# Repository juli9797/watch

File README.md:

# WATCH   

This is a simple LED-wristwatch with 16 LEDs and one push button.
Everything is controlled by a STM32F103 and its realtime clock.
Time is visualized using 12 LEDs for the hours and 5 minute steps and 4 additional LEDs to indicate minute%5 .
The current hour LED will light up steady while the minute LEDs flash slowly.

## Specs:   
* handles 1S LIPO
* 38mm diameter
* 4 Layer PCB
* exposed I2C and UART interface for future extensions

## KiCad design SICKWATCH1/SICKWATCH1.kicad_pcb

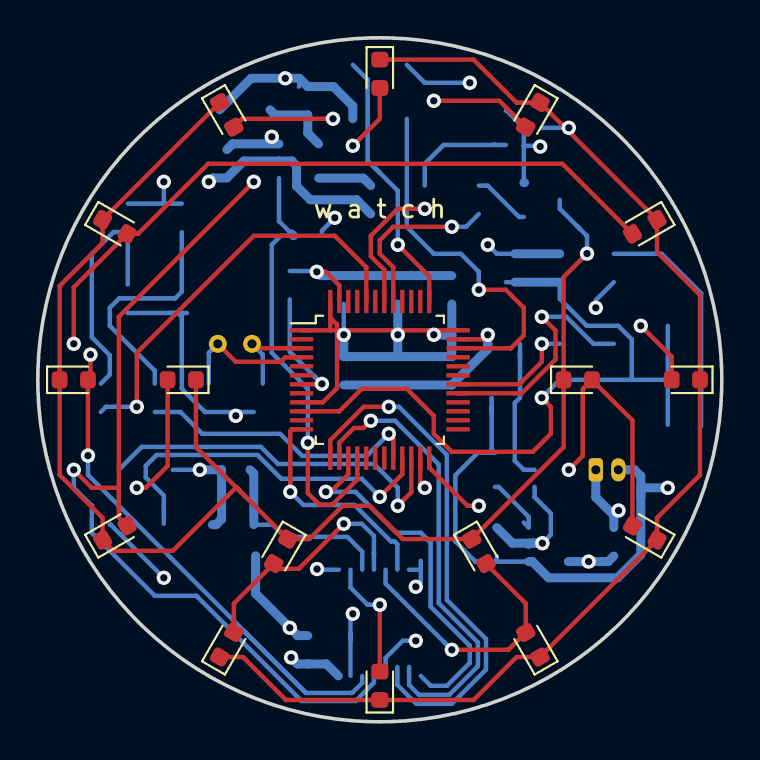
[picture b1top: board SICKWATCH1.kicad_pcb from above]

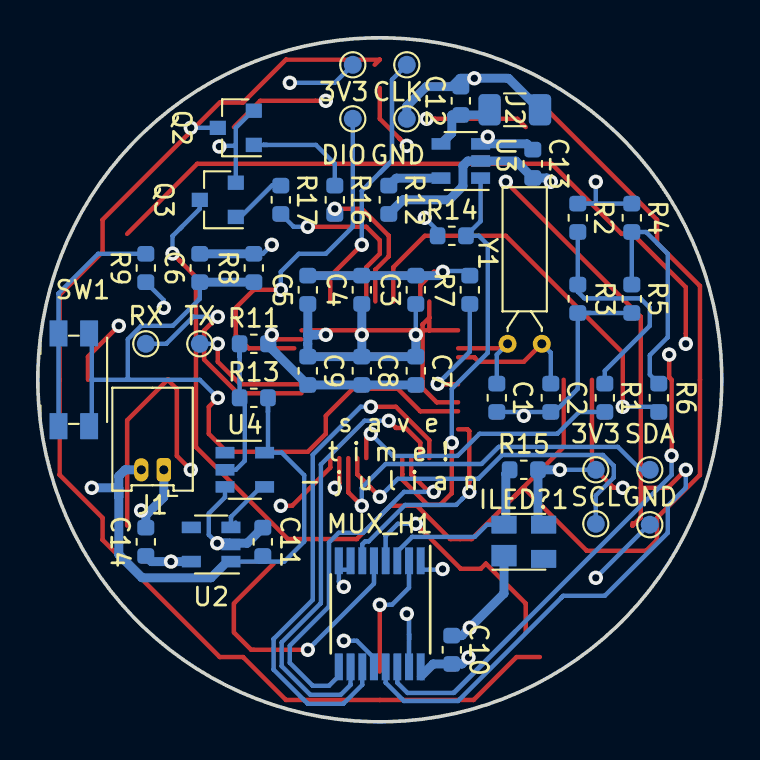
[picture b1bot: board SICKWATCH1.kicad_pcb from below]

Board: 4 copper layers, 38.0 x 38.0 mm, 68 parts (51 on the bottom side), 42 nets.

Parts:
C1, C2, C6, C10: C; C_0603_1608Metric
C3, C13: 4u7; C_0603_1608Metric
C4, C5, C7, C8, C9, C11, C14: 100n; C_0603_1608Metric
C12: 100nF; C_0603_1608Metric
D1, D2, D3, D4, D5, D6, D7, D8, D9, D10, D11, D12, D13, D14, D15, D16: LED; LED_0603_1608Metric
ILED?1: BCR401; SOT-143R_Reverse
J1: Conn_01x02_Female; Molex_PicoBlade_53048-0210_1x02_P1.25mm_Horizontal
J2: Conn_01x02_Female; R_1206_3216Metric
MUX_H1: SN74LV4051A; TSSOP-16_4.4x5mm_P0.65mm
Q2, Q3: BSS138; SOT-23
R1, R6: 100k; R_0603_1608Metric
R2, R3, R4, R5: 0; R_0603_1608Metric
R7, R8, R9, R11, R13, R15: R; R_0603_1608Metric
R12, R14: 10k; R_0603_1608Metric
R16, R17: 1k; R_0603_1608Metric
SW1: SW_Push; Panasonic_EVQPUK_EVQPUB
TP1, TP5: 3V3; TestPoint_Pad_D1.0mm
TP2: DIO; TestPoint_Pad_D1.0mm
TP3: CLK; TestPoint_Pad_D1.0mm
TP4, TP8: GND; TestPoint_Pad_D1.0mm
TP6: SDA; TestPoint_Pad_D1.0mm
TP7: SCL; TestPoint_Pad_D1.0mm
TP9: TX; TestPoint_Pad_D1.0mm
TP10: RX; TestPoint_Pad_D1.0mm
U1: STM32F103C8Tx; LQFP-48_7x7mm_P0.5mm
U2: TLV71333PDBV; SOT-23-5
U3: MCP73831-2-OT; SOT-23-5
U4: 74LVC1G17; SOT-23-5
Y1: Crystal; Crystal_C26-LF_D2.1mm_L6.5mm_Horizontal

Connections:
3V3: C3.1, C4.1, C5.1, C7.1, C8.1, C9.1, C10.1, C14.1, ILED?1.3, MUX_H1.16, R2.1, R4.1, R9.1, R14.1, R15.2, TP1.1, TP5.1, U1.1, U1.9, U1.24, U1.36, U1.48, U2.5
/Sheet5CD3F32F/WKUP: C6.1, R8.1, SW1.2, U1.10, U1.11
A0: MUX_H1.11, U1.13
A1: MUX_H1.10, U1.14
A2: MUX_H1.9, U1.15
BAT+: C11.1, C13.1, J1.2, R13.2, U2.1, U3.3, U4.5
BAT_STAT: R14.2, U1.16, U3.1
ENA: MUX_H1.6, U1.12
GND: C1.2, C2.2, C3.2, C4.2, C5.2, C6.2, C7.2, C8.2, C9.2, C10.2, C11.2, C12.2, C13.2, C14.2, ILED?1.1, J1.1, J2.2, MUX_H1.7, MUX_H1.8, Q2.2, Q3.2, R3.1, R5.2, R7.2, R8.2, R11.2, R12.2, TP4.1, TP8.1, U1.23, U1.35, U1.47, U2.2, U3.2, U4.3
K0: R16.2, U1.42
K1: R17.2, U1.41
unnamed: C1.1, U1.3, Y1.2
unnamed: C2.1, U1.4, Y1.1
unnamed: D1.1, D2.1, D3.1, D4.1, D5.1, D6.1, D7.1, D8.1, Q2.3
unnamed: D1.2, D9.2, MUX_H1.13
unnamed: D9.1, D10.1, D11.1, D12.1, D13.1, D14.1, D15.1, D16.1, Q3.3
unnamed: D2.2, D10.2, MUX_H1.14
unnamed: D3.2, D11.2, MUX_H1.15
unnamed: D4.2, D12.2, MUX_H1.12
unnamed: D5.2, D13.2, MUX_H1.1
unnamed: D6.2, D14.2, MUX_H1.5
unnamed: D7.2, D15.2, MUX_H1.2
unnamed: D8.2, D16.2, MUX_H1.4
unnamed: Q2.1, R16.1
unnamed: Q3.1, R17.1
unnamed: R1.1, R2.2, R3.2
unnamed: R1.2, U1.20
unnamed: R4.2, R5.1, R6.2
unnamed: R6.1, U1.44
unnamed: R7.1, U1.7
unnamed: R9.2, SW1.1
unnamed: R11.1, R13.1, U4.2
unnamed: R12.1, U3.5
unnamed: U2.3, U4.4
RX: TP10.1, U1.29
SCL: TP7.1, U1.21
SDA: TP6.1, U1.22
SWCLK: TP3.1, U1.37
SWDIO: TP2.1, U1.34
TX: TP9.1, U1.30
ULED: ILED?1.2, MUX_H1.3, R15.1
V_IN: C12.1, J2.1, U3.4

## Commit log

2019-11-22 finished layout
2019-11-22 fixed screenprints
2019-11-27 Layout done (I GUESS)
2019-11-28 finished V1.0 and ordered pcbs
2019-11-28 cleanup
2019-11-28 more cleanup
2019-11-28 changed README
